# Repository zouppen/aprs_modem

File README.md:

# aprs_modem
APRS modem using ATmega32u4 and HX1 radio module

## License

This program is free software: you can redistribute it and/or modify
it under the terms of the GNU Affero General Public License as
published by the Free Software Foundation, either version 3 of the
License, or (at your option) any later version.

This program is distributed in the hope that it will be useful, but
WITHOUT ANY WARRANTY; without even the implied warranty of
MERCHANTABILITY or FITNESS FOR A PARTICULAR PURPOSE.  See the GNU
Affero General Public License for more details.

You should have received a copy of the GNU Affero General Public
License along with this program.  If not, see
<http://www.gnu.org/licenses/>.

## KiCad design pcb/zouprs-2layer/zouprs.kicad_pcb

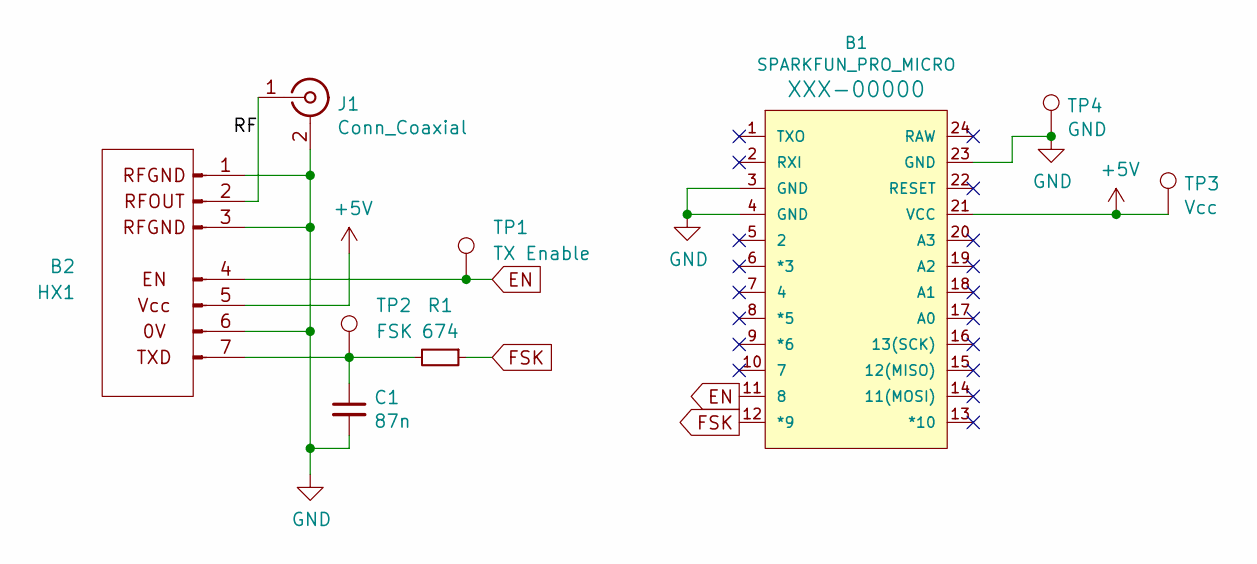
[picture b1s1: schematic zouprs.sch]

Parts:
B1: SPARKFUN_PRO_MICRO
B2: HX1; PinHeader_1x12_P2.54mm_Vertical
C1: 87n; C_1206_3216Metric_Pad1.42x1.75mm_HandSolder
J1: Conn_Coaxial; SMA_Samtec_SMA-J-P-X-ST-EM1_EdgeMount
R1: 674; R_1206_3216Metric_Pad1.42x1.75mm_HandSolder
TP1: TX Enable; TestPoint_Pad_D1.0mm
TP2: FSK; TestPoint_Pad_D1.0mm
TP3: Vcc; TestPoint_Pad_D1.0mm
TP4: GND; TestPoint_Pad_D1.0mm

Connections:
+5V: B1.21 (VCC), B2.5 (GND), TP3.1
EN: B1.11 (8), B2.4 (EN), TP1.1
FSK: B1.12 (*9), R1.1
GND: B1.3 (GND), B1.4 (GND), B1.23 (GND), B2.1 (RFGND), B2.3 (RFGND), B2.6 (VCC), C1.2, J1.2 (Ext), TP4.1
unnamed: B2.2 (RFOUT), J1.1 (In)
unnamed: B2.7 (TXD), C1.1, R1.2, TP2.1

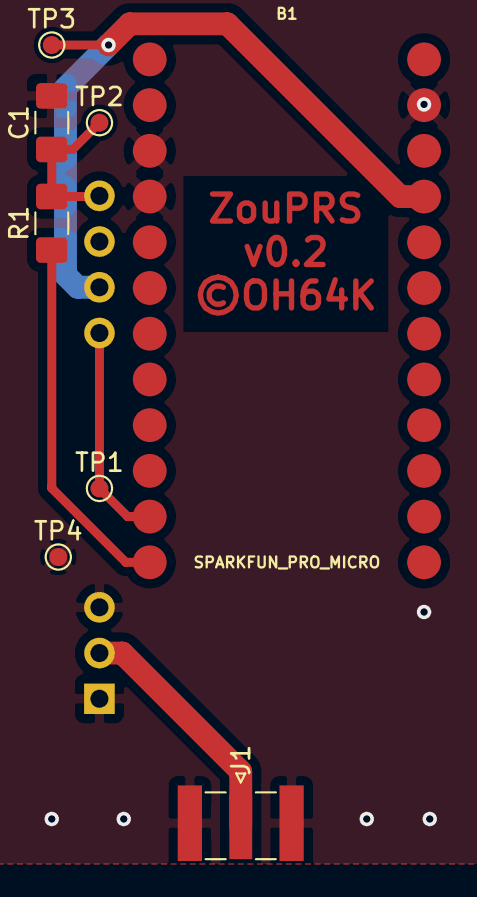
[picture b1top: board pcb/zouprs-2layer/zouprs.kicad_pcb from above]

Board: 2 copper layers, 9 parts (1 on the bottom side), 6 nets.

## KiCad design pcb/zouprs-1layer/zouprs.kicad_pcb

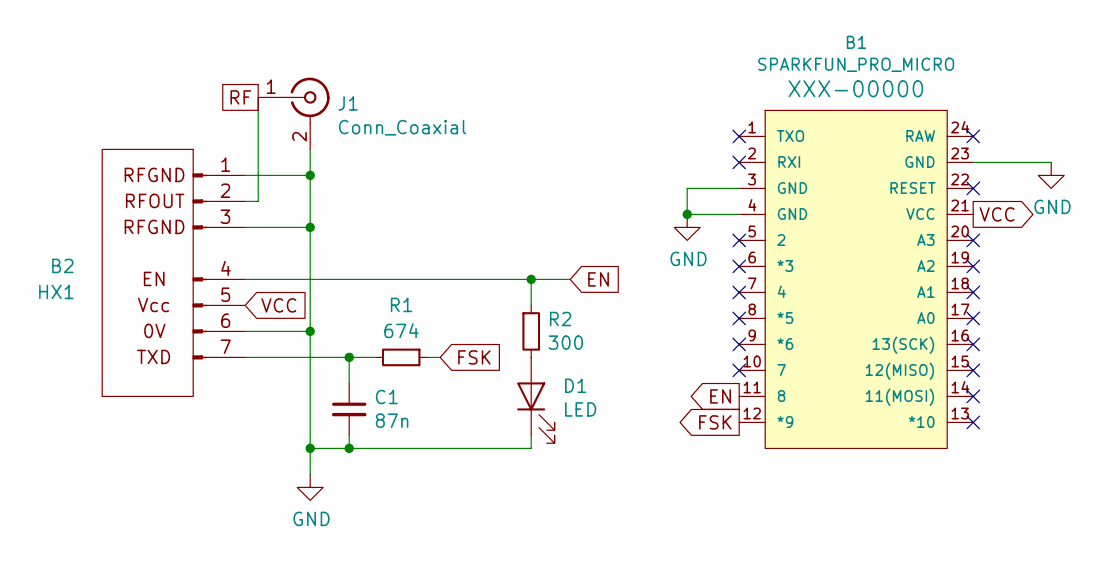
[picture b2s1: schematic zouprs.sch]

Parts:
B1: SPARKFUN_PRO_MICRO
B2: HX1; PinHeader_1x12_P2.54mm_Vertical
C1: 87n; C_Rect_L7.0mm_W2.5mm_P5.00mm
D1: LED; PinHeader_1x02_P2.54mm_Vertical
J1: Conn_Coaxial; SMA_Samtec_SMA-J-P-X-ST-EM1_EdgeMount
R1: 674; R_Axial_DIN0207_L6.3mm_D2.5mm_P10.16mm_Horizontal
R2: 300; R_Axial_DIN0207_L6.3mm_D2.5mm_P2.54mm_Vertical

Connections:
EN: B1.11 (8), B2.4 (EN), R2.1
FSK: B1.12 (*9), R1.1
GND: B1.3 (GND), B1.4 (GND), B1.23 (GND), B2.1 (RFGND), B2.3 (RFGND), B2.6 (VCC), C1.2, D1.1 (K), J1.2 (Ext)
unnamed: B2.7 (TXD), C1.1, R1.2
unnamed: D1.2 (A), R2.2
RF: B2.2 (RFOUT), J1.1 (In)
VCC: B1.21 (VCC), B2.5 (GND)

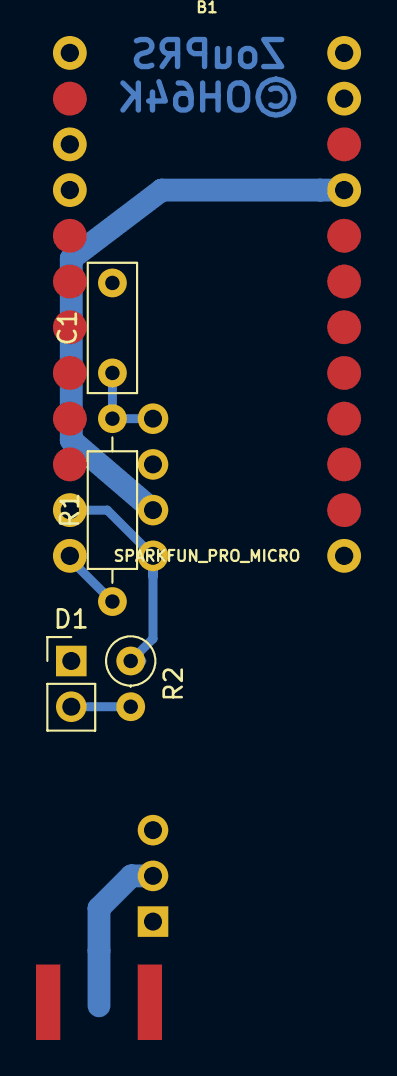
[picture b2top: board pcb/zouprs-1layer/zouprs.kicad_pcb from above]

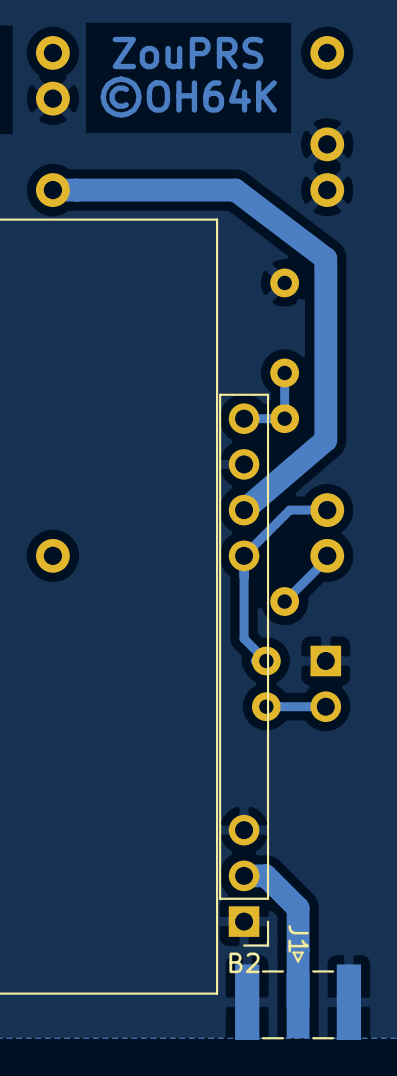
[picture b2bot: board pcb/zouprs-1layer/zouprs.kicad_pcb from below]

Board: 2 copper layers, 7 parts (2 on the bottom side), 7 nets.

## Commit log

2017-09-05 Initial version of USB KISS TNC
2020-09-29 Make it support new ZouPRS board
2020-09-30 Enclosure added
2020-09-30 minor tweaks
2020-10-01 Add PCB
2020-10-03 Make dual side PCB
2020-10-03 Move Arduino board about 1mm up
2020-10-03 Add some ground vias to RF end of the board
2020-10-03 Small tweaks to test point
2020-10-06 Add simple "powerpolish" plug
2020-10-06 Outer dimensions match
2020-10-06 Add double powerpolish
2020-10-06 Add tongue
2020-10-06 Add some comments to the variables
2020-10-07 Add support for parametric pole arrays
2020-10-07 Add wedges for easier printing
2020-10-07 Tongue at too back, blocking the connector. Fixing.
2020-10-07 Add support for framing
2020-10-07 Add framing support for poles (case mount)
2020-10-08 Fix back wedge so that it's not inside back wall
2020-10-08 Fine-tune lower cup lower wall thickness. Calculate it form back wall thickness
2020-10-08 Make different kind of tongue to PCB mount block
2020-10-08 Fix slope math in wedges
2020-10-08 Add support for protective cap for Anderson Powerpole
2020-10-09 enclosure: Make cup of the cap filled to top
2020-10-09 enclosure: Tongue must be thicker to not to break
2020-10-09 enclosure: Connector support should be higher and the round hole larger
2020-10-09 enclosure: Move parametric model to a separate file

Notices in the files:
pcb/zouprs-1layer/zouprs.kicad_pcb:
©OH64K
